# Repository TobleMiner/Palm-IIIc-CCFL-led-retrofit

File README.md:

Palm IIIc LED backlight replacement
===================================

This repo contains a PCB designed to replace the CCFL backlight of Palm
IIIc PDAs with a LED based backlight.  
The LED based backlight can provide higher fidelity of displayed colors
and prolonged battery runtime.

# LED PCB

## Top

## Bottom

# Assembly

Assembly of the PCB can be a bit of a tedious job since both the board and
components are relatively small. I recommend either pretinning the pads on
the PCB and applying liberal amounts of flux to stick the components into
place or using solder paste. Using hot air at a low airflow setting the
components can then be reflowed into place.  
For connecting the power supply wiring it is best to connect one wire on
the top and one at the back opposite to the first wire. Use thin enamel
wire (~0.2 mm diameter) to ensure there are no fitment problems after
installation into the Palm.

# Installation

As a first step the Palm has to be fully disassembled. This includes
removing the bare LCD cell from the LCD assembly. After removal of the LCD
cell the white tape over the CCFL tube in the white backlight diffuser
assembly can be pulled up. Then the CCFL tube can be removed.  
Next the assembled LED PCB can be placed into the diffuser assembly in the
same spot where the CCFL tube was previously located. After reassembly of
the LCD assembly it can be placed back into the case, also reassembling
the midframe.  
Finally it is necessary to perform a small modification of the Palm's 
mainboard to disable the original CCFL inverter and enable control of the
LED backlight.  
The Palm IIIc employs a LX1686CPW CCFL controller for backlight control.
The PWM signal controlling backlight brightness can be tapped of Pin 11
on the IC.  
To minimize overall weight of the Palm I choose to remove the CCFL
backlight transformer to disable the original backlight.  
To allow for control of the new LED backlight a small MOSFET has to be
added to the mainboard. On my Palm IIIc I used a 2N7002K, a good option
due to low gate charge and relatively low RdsOn. The complete mod can be
seen in the following picture:

Here I just connected the MOSFET source to GND on a conveniently placed
capacitor to fix it in place. I then connected the PWM backlight control
signal from pin 11 on the CCFL controller IC to the MOSFET gate. Finally
I connected the negative LED board connection to the MOSFET's drain and
the positive LED board connection to a large testpoint providing direct B+
battery power next to the battery connector.

# Results

After installing this mod the backlight is substantially brighter and
reaches full brightness immediately after waking up the Palm. Also colors
look a lot more vibrant. The following photo tries to capture how good the
colors look but really does not quite do the improvement justice.

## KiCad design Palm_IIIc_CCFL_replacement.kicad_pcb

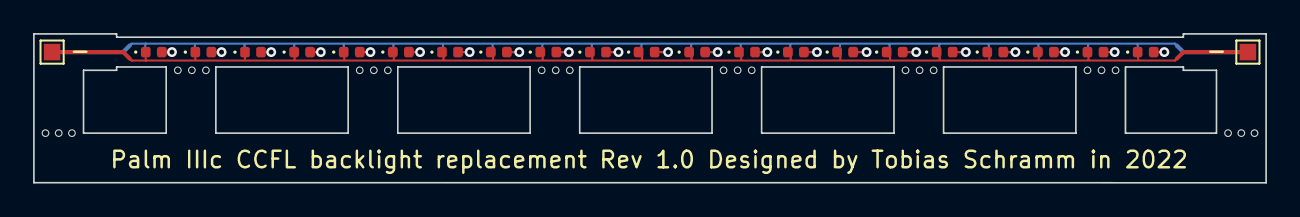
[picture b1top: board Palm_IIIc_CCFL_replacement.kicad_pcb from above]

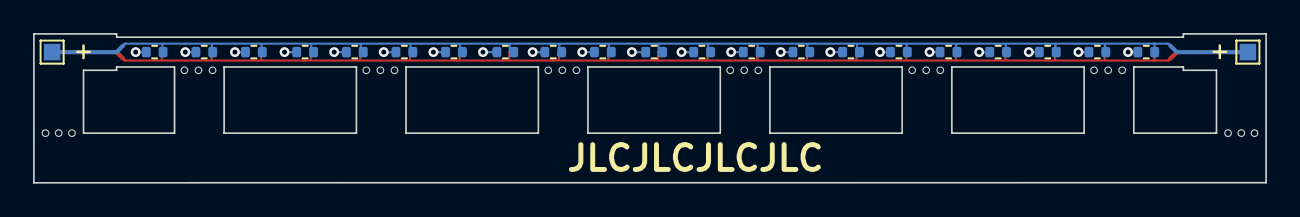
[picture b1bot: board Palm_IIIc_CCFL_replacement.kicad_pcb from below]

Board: 2 copper layers, 74.5 x 9.0 mm, 56 parts (23 on the bottom side), 23 nets.

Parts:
1, 2, 3, 4, 5, 6, 7, 8, 9, 10: (no value)
D1, D2, D3, D4, D5, D6, D7, D8, D9, D10, D11, D12, D13, D14, D15, D16, D17, D18, D19, D20, D21: White; D_0402_1005Metric
R1, R2, R3, R4, R5, R6, R7, R8, R9, R10, R11, R12, R13, R14, R15, R16, R17, R18, R19, R20, R21: 330R; R_0402_1005Metric
TP1, TP2, TP3, TP4: TestPoint; TestPoint_Pad_1.0x1.0mm

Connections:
GND: D1.1 (K), D2.1 (K), D3.1 (K), D4.1 (K), D5.1 (K), D6.1 (K), D7.1 (K), D8.1 (K), D9.1 (K), D10.1 (K), D11.1 (K), D12.1 (K), D13.1 (K), D14.1 (K), D15.1 (K), D16.1 (K), D17.1 (K), D18.1 (K), D19.1 (K), D20.1 (K), D21.1 (K), TP1.1, TP2.1
unnamed: D1.2 (A), R1.2
unnamed: D2.2 (A), R2.2
unnamed: D3.2 (A), R3.2
unnamed: D4.2 (A), R4.2
unnamed: D5.2 (A), R5.2
unnamed: D6.2 (A), R6.2
unnamed: D7.2 (A), R7.2
unnamed: D8.2 (A), R8.2
unnamed: D9.2 (A), R9.2
unnamed: D10.2 (A), R10.2
unnamed: D11.2 (A), R11.2
unnamed: D12.2 (A), R12.2
unnamed: D13.2 (A), R13.2
unnamed: D14.2 (A), R14.2
unnamed: D15.2 (A), R15.2
unnamed: D16.2 (A), R16.2
unnamed: D17.2 (A), R17.2
unnamed: D18.2 (A), R18.2
unnamed: D19.2 (A), R19.2
unnamed: D20.2 (A), R20.2
unnamed: D21.2 (A), R21.2
VBUS: R1.1, R2.1, R3.1, R4.1, R5.1, R6.1, R7.1, R8.1, R9.1, R10.1, R11.1, R12.1, R13.1, R14.1, R15.1, R16.1, R17.1, R18.1, R19.1, R20.1, R21.1, TP3.1, TP4.1

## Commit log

2022-03-26 Add additional supports to PCB
2022-05-14 Add README
2022-05-14 Fix PCB bottom side render
2022-05-15 README: elaborate on MOSFET installation procedure
2022-05-15 README: improve wording
2022-05-15 README: fix typos
2022-05-15 Add schematic export
